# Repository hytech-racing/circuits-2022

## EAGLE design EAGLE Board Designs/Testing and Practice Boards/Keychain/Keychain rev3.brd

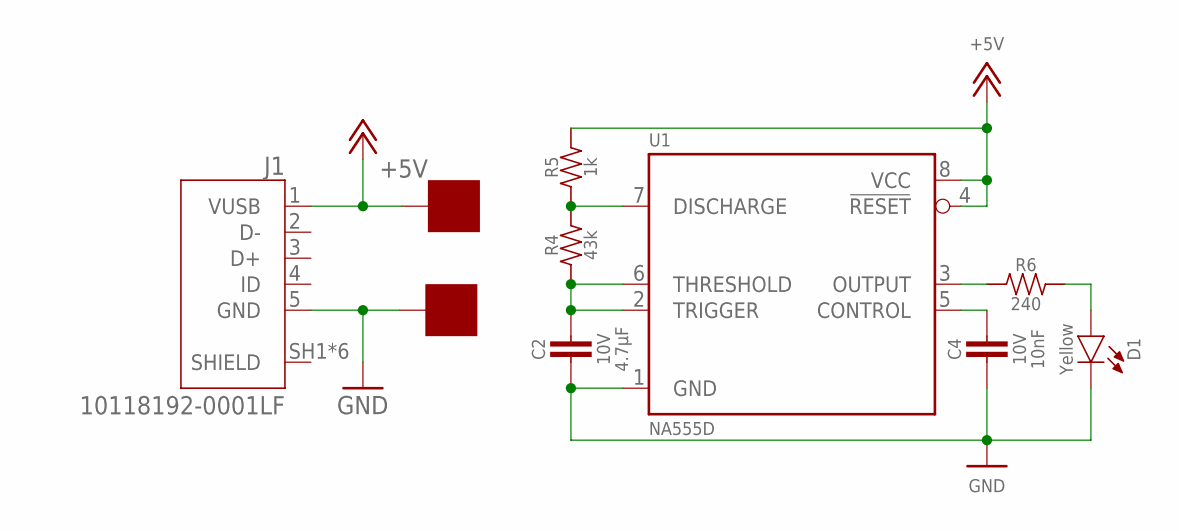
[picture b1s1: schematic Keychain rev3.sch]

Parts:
5V: SOLDER_PAD; SOLDER_PAD_XSMALL
C2: CAPACITOR_0603_10V_4.7UF; 0603-CAP
C4: CAPACITOR_0603_10V_10NF; 0603-CAP
D1: LED_0603_YELLOW; 0603-LED
GND: SOLDER_PAD; SOLDER_PAD_XSMALL
J1: 10118192-0001LF; AMPHENOL_10118192-0001LF
R4: RESISTOR_0603_43K; 0603-RES
R5: RESISTOR_0603_1K; 0603-RES
R6: RESISTOR_0603_240; 0603-RES
U1: NA555; SOIC-08(NARROW,0.15")

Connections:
+5V: 5V.P$1, J1.1 (VUSB), R5.2, U1.4 (!RESET), U1.8 (VCC)
GND: C2.2, C4.2, D1.1 (C), GND.P$1, J1.5 (GND), U1.1 (GND)
unnamed: C2.1, R4.1, U1.2 (TRIGGER), U1.6 (THRESHOLD)
unnamed: R4.2, R5.1, U1.7 (DISCHARGE)
unnamed: R6.1, U1.3 (OUTPUT)
unnamed: D1.2 (A), R6.2
unnamed: C4.1, U1.5 (CONTROL)

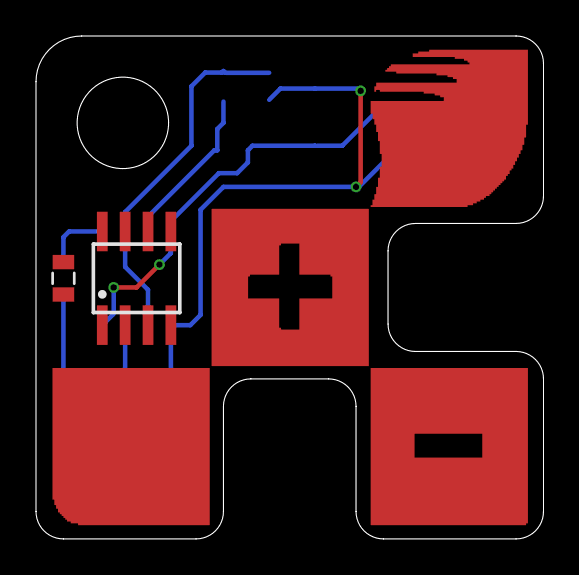
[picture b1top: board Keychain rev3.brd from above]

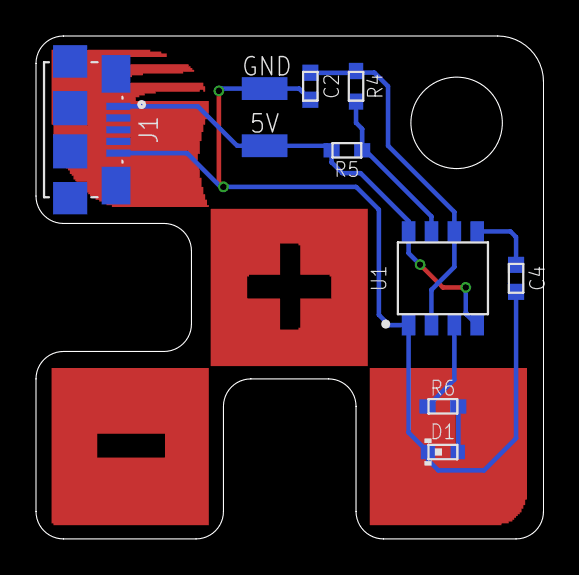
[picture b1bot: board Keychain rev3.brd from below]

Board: 2 copper layers, 28.2 x 27.9 mm, 12 parts (10 on the bottom side), 7 nets.

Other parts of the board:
E$1: 0805@1
E$2: SOIC-08

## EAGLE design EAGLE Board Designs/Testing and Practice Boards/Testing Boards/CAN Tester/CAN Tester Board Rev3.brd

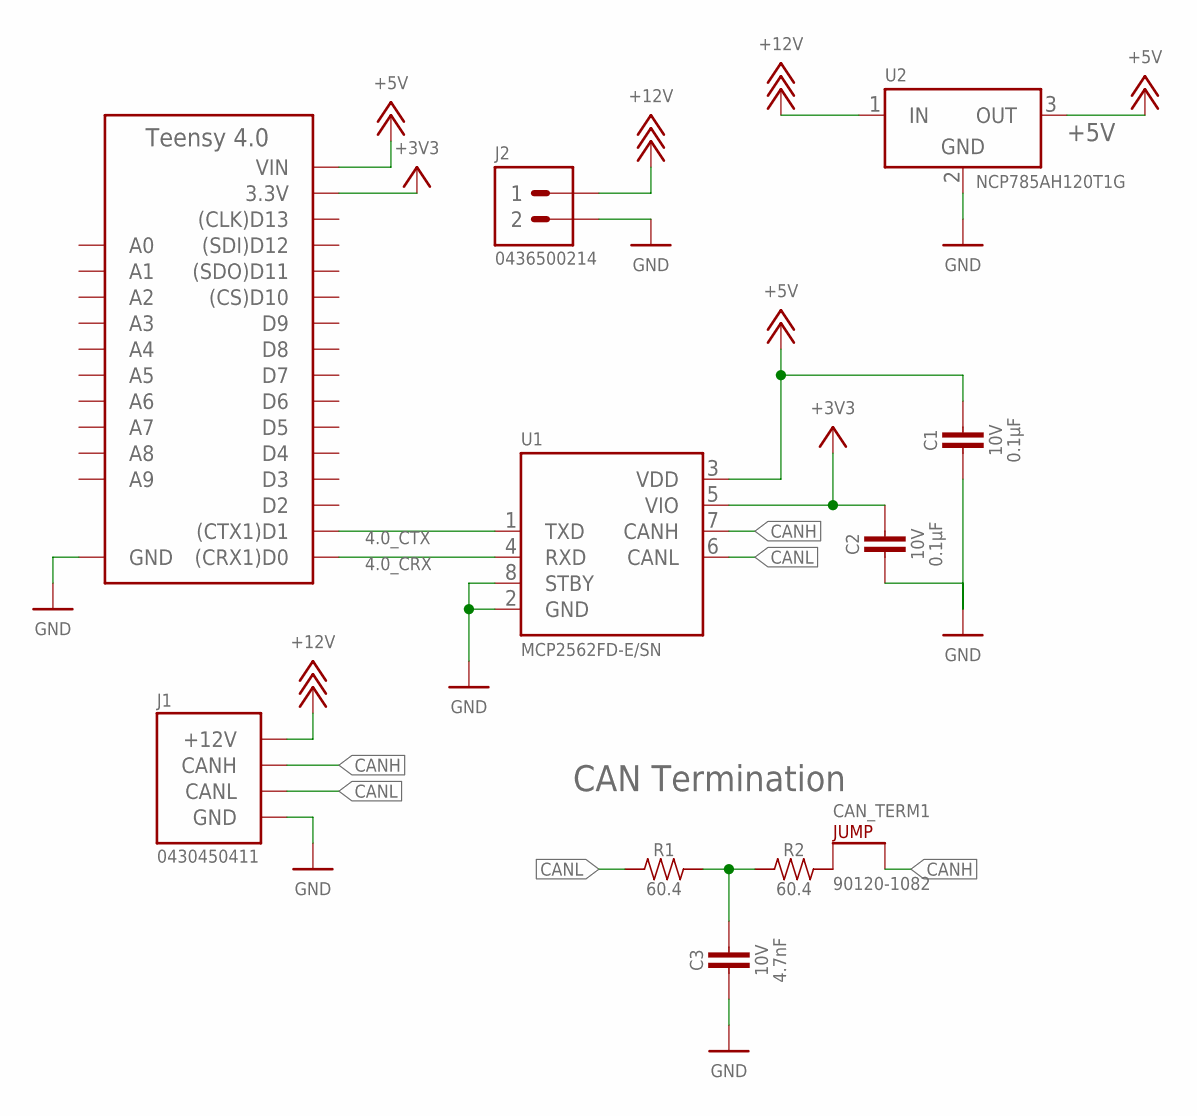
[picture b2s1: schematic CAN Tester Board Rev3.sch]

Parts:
A1: TEENSY_4.0; TEENSY_SHORT
C1, C2: CAPACITOR_0603_10V_0.1UF; 0603-CAP
C3: CAPACITOR_0603_10V_4.7NF; 0603-CAP
CAN_TERM1: JUMPER__1X02; 1X02
J1: CONNECTOR-CAN_μF_S_RA_; MOLEX_MICROFIT_SMD_RIGHTANGLE_04_DUAL
J2: CONNECTOR-2_MICROFIT_SMD_RIGHTANGLE_02_SINGLE_BLA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; MOLEX_MICROFIT_SMD_RIGHTANGLE_02_SINGLE
R1, R2: RESISTOR_0603_60.4; 0603-RES
U1: MCP2562FD; SOIC-08(NARROW,0.15")
U2: VOLTAGE_REGULATOR_SOT-89_12V; SOT-89

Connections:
4.0_CRX: A1.D0 ((CRX1)D0), U1.4 (RXD)
4.0_CTX: A1.D1 ((CTX1)D1), U1.1 (TXD)
+3V3: A1.3.3V, C2.1, U1.5 (VIO)
+5V: A1.VIN, C1.1, U1.3 (VDD), U2.3 (OUT)
+12V: J1.1 (+12V), J2.1, U2.1 (IN)
CANH: CAN_TERM1.2, J1.4 (CANH), U1.7 (CANH)
CANL: J1.3 (CANL), R1.1, U1.6 (CANL)
GND: A1.AGND/GND (GND), A1.GND, C1.2, C2.2, C3.2, J1.2 (GND), J2.2, U1.2 (GND), U1.8 (STBY), U2.2 (GND)
unnamed: C3.1, R1.2, R2.1
unnamed: CAN_TERM1.1, R2.2

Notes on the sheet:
CAN Termination

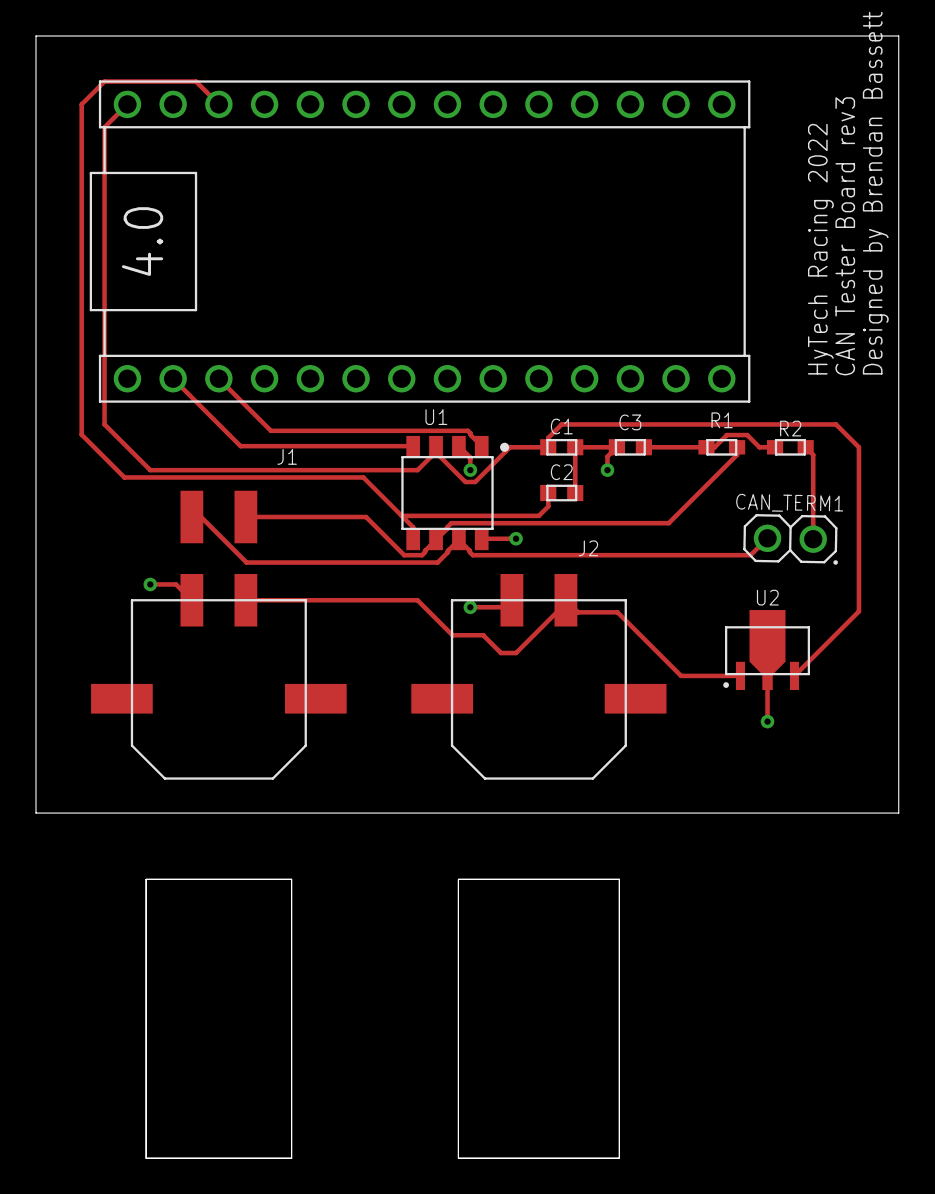
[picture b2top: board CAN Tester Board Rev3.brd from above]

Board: 2 copper layers, 47.9 x 43.2 mm, 11 parts (0 on the bottom side), 10 nets.

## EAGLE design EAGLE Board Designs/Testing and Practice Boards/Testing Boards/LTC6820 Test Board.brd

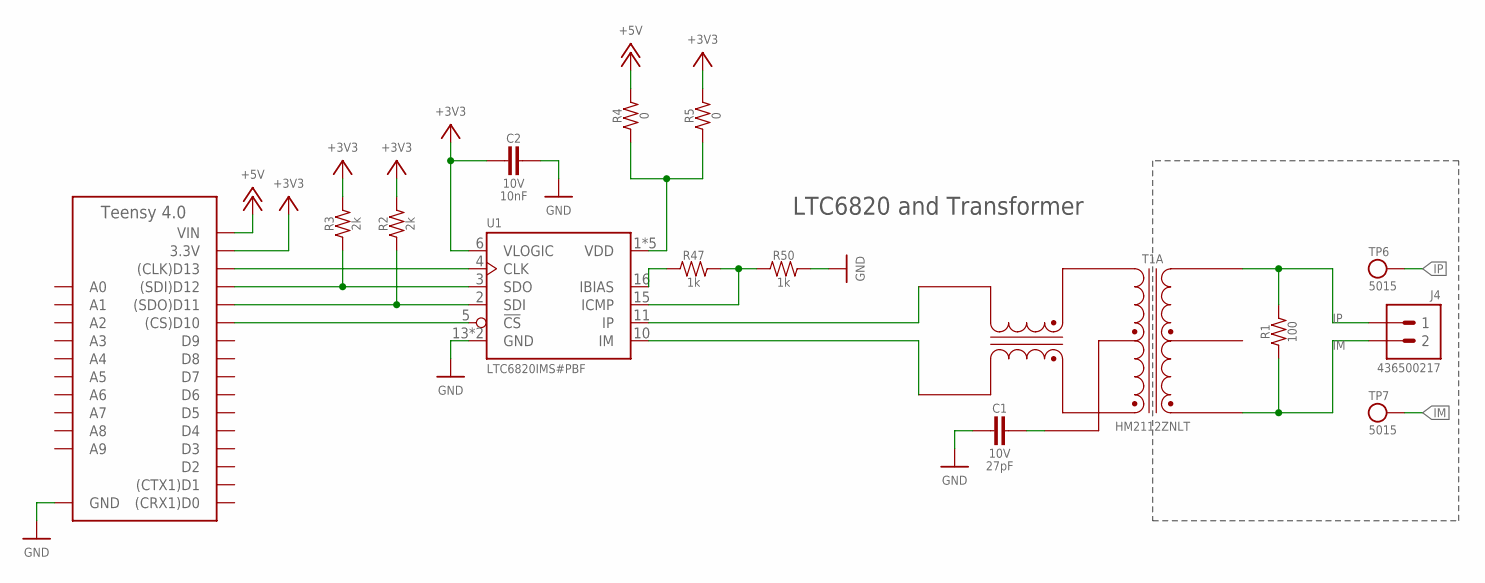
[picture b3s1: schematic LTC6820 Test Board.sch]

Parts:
A1: TEENSY_4.0; TEENSY_SHORT
C1: CAPACITOR_0603_10V_27PF; 0603-CAP
C2: CAPACITOR_0603_10V_10NF; 0603-CAP
J4: CONNECTOR-2_MF_T_V_; MOLEX_MICROFIT_PTH_VERTICAL_02_SINGLE
R1: RESISTOR_0603_100; 0603-RES
R2, R3: RESISTOR_0603_2K; 0603-RES
R4, R5: RESISTOR_0603_0; 0603-RES
R47, R50: RESISTOR_0603_1K; 0603-RES
T1: TRANSFORMER_HM2112ZNLT_AIRGAP; HM2112ZNLT_AIRGAP
TP6, TP7: TEST_POINT; MICRO_MINIATURE
U1: LTC6820; MSOP-16

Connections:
+3V3: A1.3.3V, C2.2, R2.2, R3.2, R5.2, U1.6 (VLOGIC)
+5V: A1.VIN, R4.2
GND: A1.AGND/GND (GND), A1.GND, C1.2, C2.1, R50.2, U1.13 (GND), U1.14 (GND)
IM: J4.2, R1.1, T1.1 (MX+), TP7.1
IP: J4.1, R1.2, T1.3 (MX-), TP6.1
unnamed: C1.1, T1.11 (TCT)
unnamed: A1.D13 ((CLK)D13), U1.4 (CLK)
unnamed: A1.D12 ((SDI)D12), R3.1, U1.3 (SDO)
unnamed: A1.D11 ((SDO)D11), R2.1, U1.2 (SDI)
unnamed: A1.D10 ((CS)D10), U1.5 (!CS)
unnamed: R4.1, R5.1, U1.1 (VDD), U1.7 (VDD), U1.8 (VDD), U1.9 (VDD), U1.12 (VDD)
unnamed: T1.10 (TD-), U1.11 (IP)
unnamed: R47.1, U1.16 (IBIAS)
unnamed: R47.2, R50.1, U1.15 (ICMP)
unnamed: T1.12 (TD+), U1.10 (IM)

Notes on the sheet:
LTC6820 and Transformer

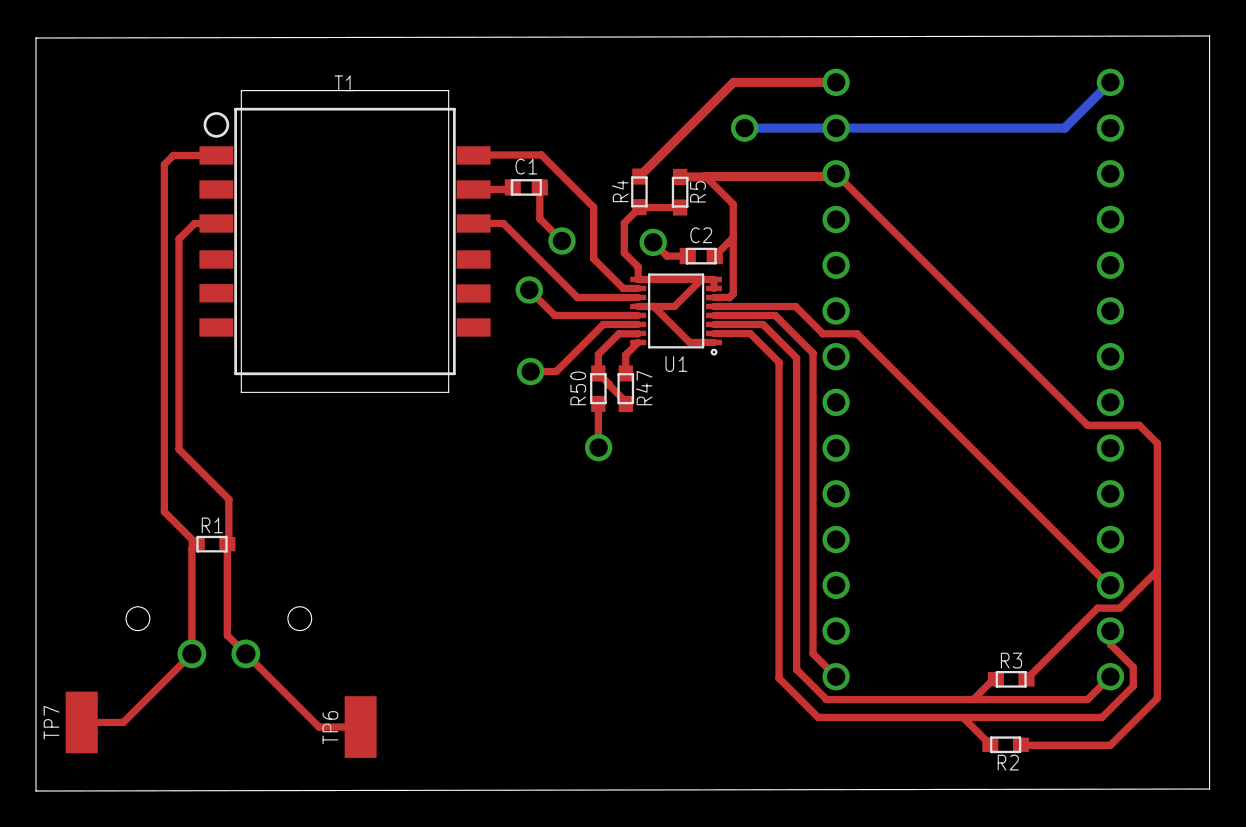
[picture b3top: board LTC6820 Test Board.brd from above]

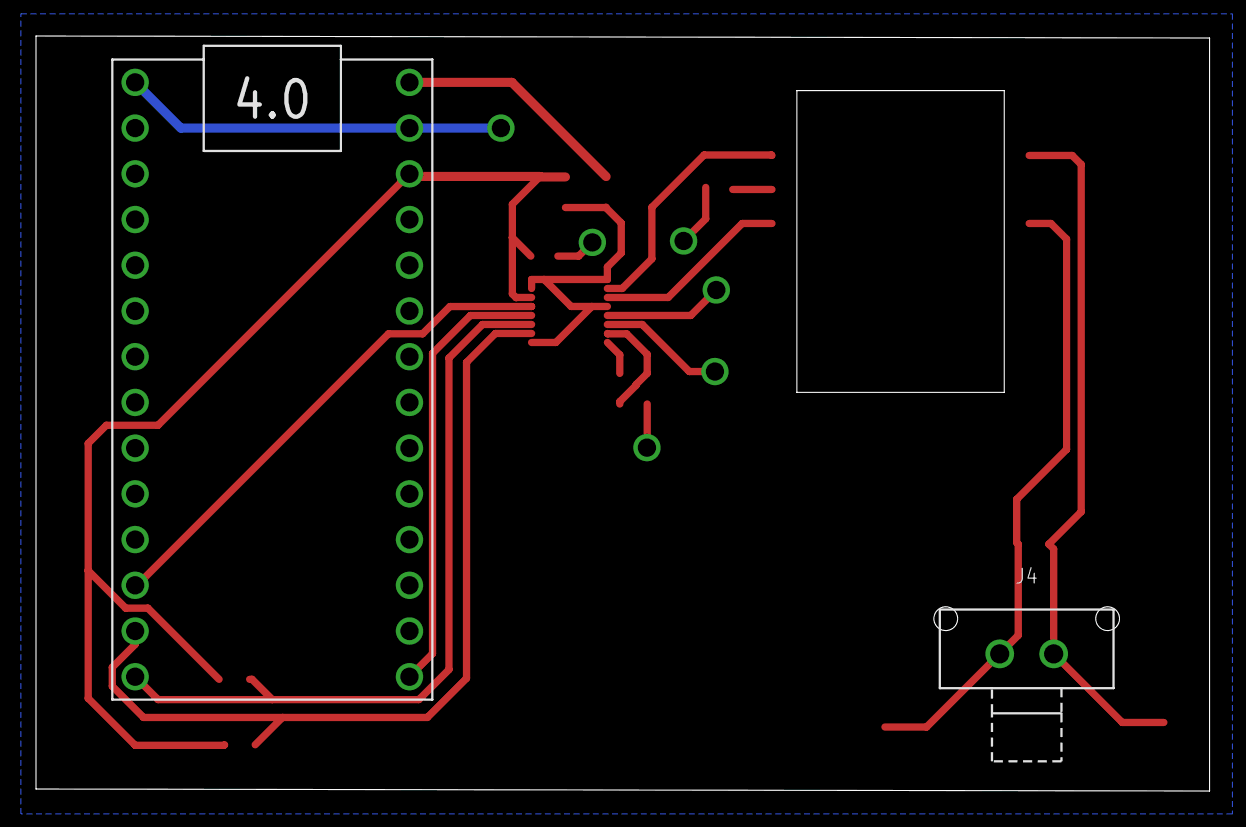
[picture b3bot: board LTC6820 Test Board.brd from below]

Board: 2 copper layers, 65.2 x 41.9 mm, 15 parts (2 on the bottom side), 15 nets.

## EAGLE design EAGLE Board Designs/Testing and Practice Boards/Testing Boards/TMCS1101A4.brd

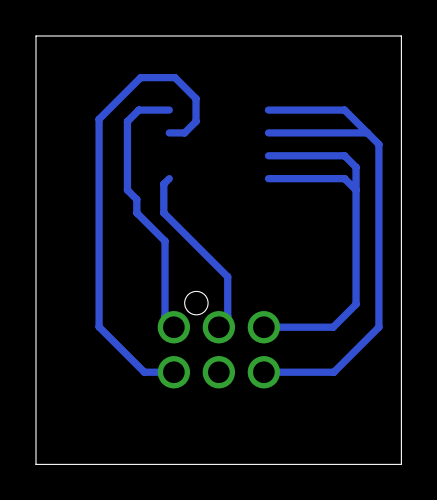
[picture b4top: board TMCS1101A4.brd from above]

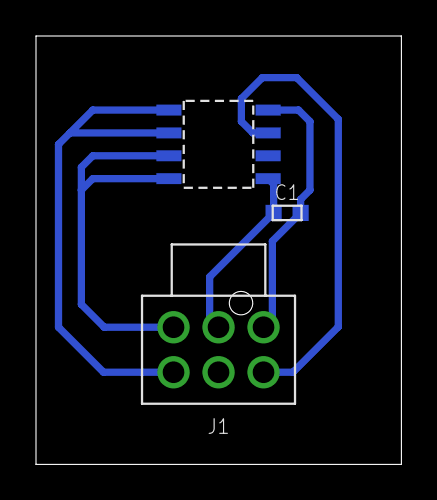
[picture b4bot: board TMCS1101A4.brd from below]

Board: 2 copper layers, 20.3 x 23.8 mm, 3 parts (3 on the bottom side), 5 nets.

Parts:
C1: CAPACITOR_0603_10V_0.1UF; 0603-CAP
J1: CONNECTOR-6_NF_T_V_BLACK; MOLEX_NANOFIT_PTH_06
U$1: TMCS1101A4; SOIC8

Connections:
+5V: C1.2, J1.1, U$1.P$8
GND: C1.1, J1.2, U$1.P$5
IN+: J1.6, U$1.P$1, U$1.P$2
IN-: J1.3, U$1.P$3, U$1.P$4
VOUT: J1.4, U$1.P$7

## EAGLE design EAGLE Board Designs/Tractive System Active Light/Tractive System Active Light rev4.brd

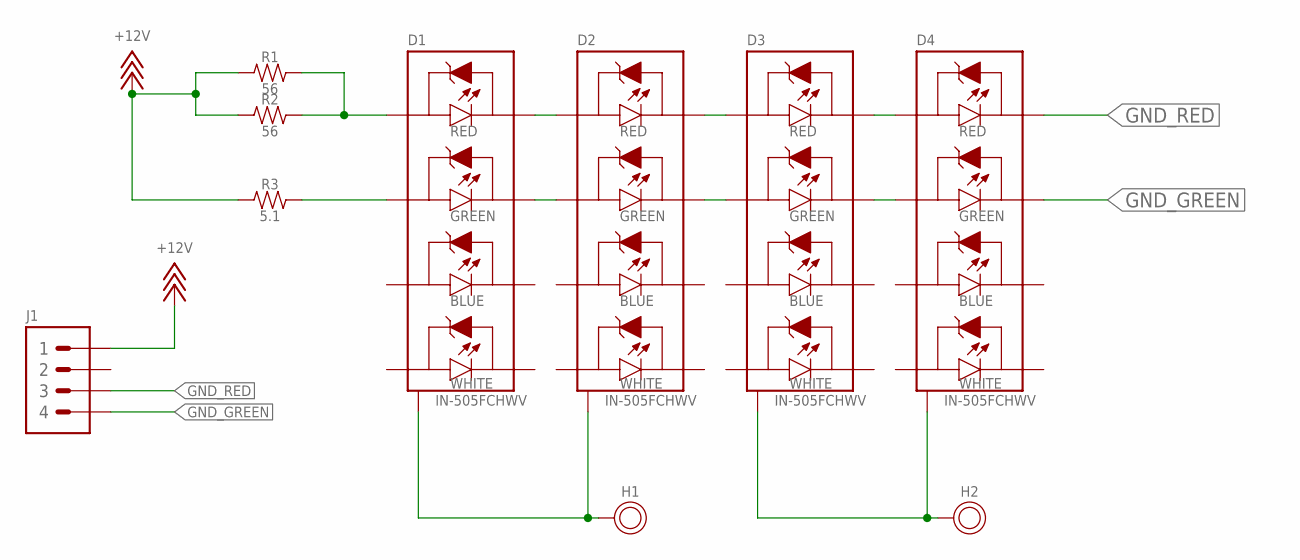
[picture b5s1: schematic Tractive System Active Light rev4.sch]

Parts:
D1, D2, D3, D4: LED_RGBW_IN-505FCHWV; IN-505FCHWV
H1, H2: MOUNTING_HEATSINK_M3; MOUNTING_M3
J1: CONNECTOR-4_μF_S_RA_; MOLEX_MICROFIT_SMD_RIGHTANGLE_04_DUAL
R1, R2: RESISTOR_0805_56; 0805-RES
R3: RESISTOR_0603_5.1; 0603-RES

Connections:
+12V: J1.1, R1.1, R2.1, R3.1
GND_GREEN: D4.B- (GREEN-), J1.4
GND_RED: D4.A- (RED-), J1.3
unnamed: D3.A- (RED-), D4.A+ (RED+)
unnamed: D3.B- (GREEN-), D4.B+ (GREEN+)
unnamed: D2.A- (RED-), D3.A+ (RED+)
unnamed: D2.B- (GREEN-), D3.B+ (GREEN+)
unnamed: D1.A- (RED-), D2.A+ (RED+)
unnamed: D1.B- (GREEN-), D2.B+ (GREEN+)
unnamed: D1.A+ (RED+), R1.2, R2.2
unnamed: D1.THERMAL, D2.THERMAL, H1.P$1
unnamed: D1.B+ (GREEN+), R3.2
unnamed: D3.THERMAL, D4.THERMAL, H2.P$1

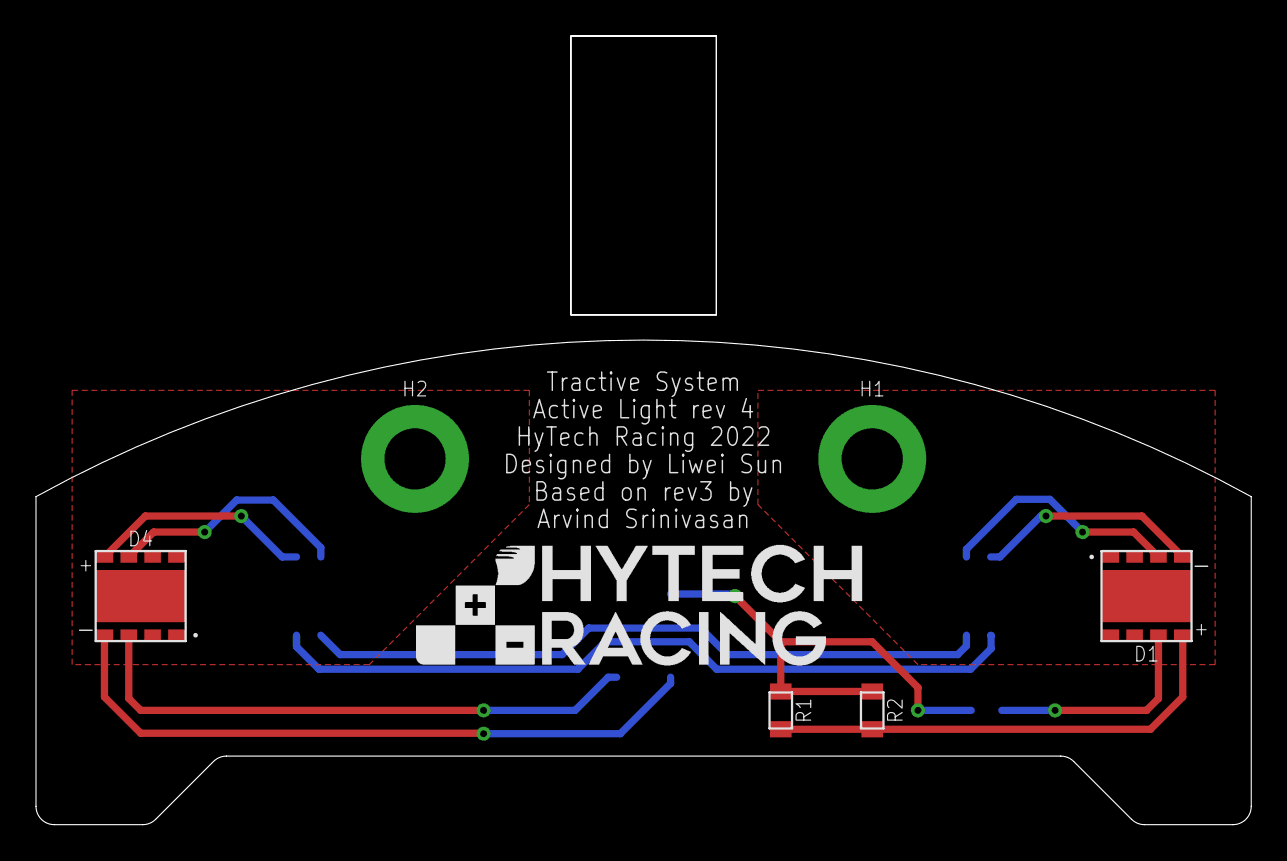
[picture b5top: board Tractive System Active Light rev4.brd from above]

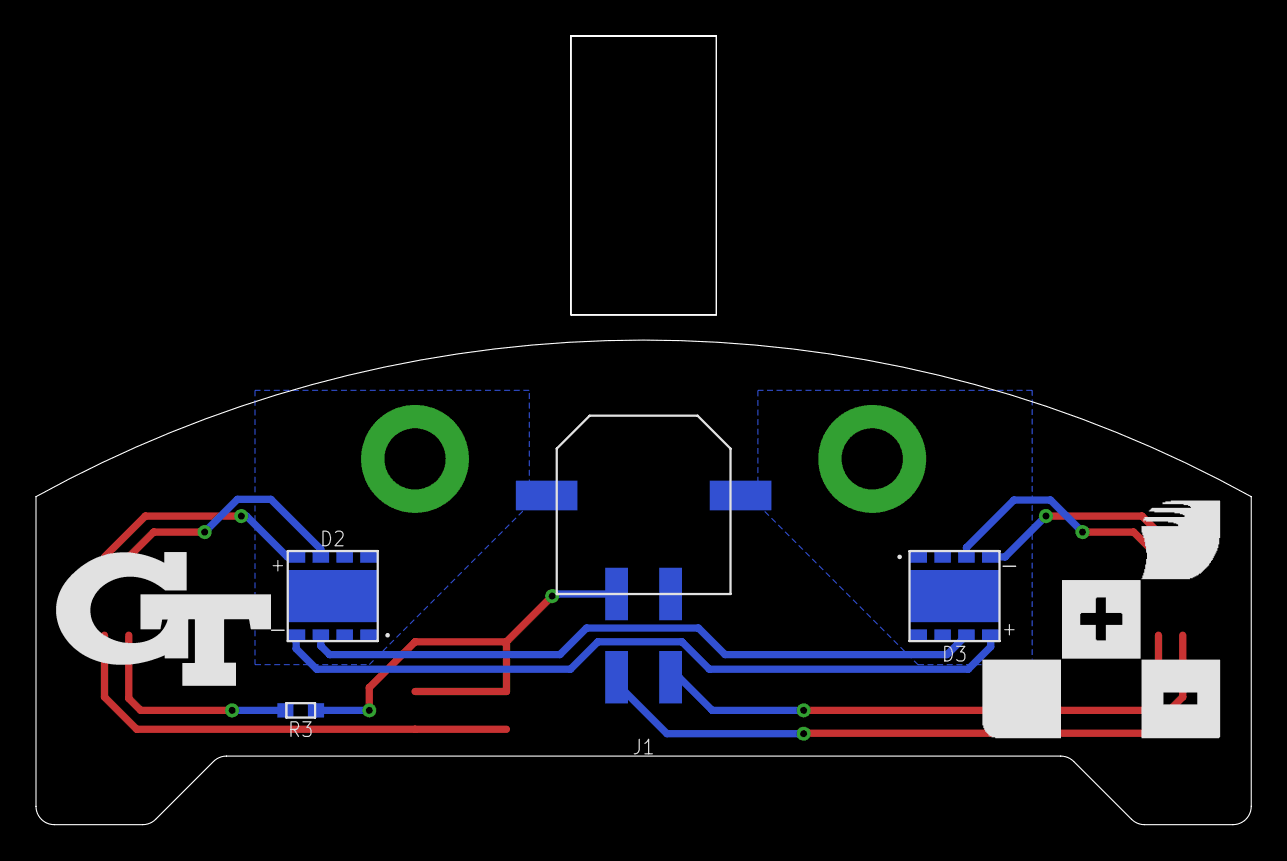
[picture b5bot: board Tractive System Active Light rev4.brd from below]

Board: 2 copper layers, 67.5 x 26.9 mm, 13 parts (6 on the bottom side), 13 nets.

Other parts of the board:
U$1: LOGO_HYTECH_SQUARE_EXTRA_LARGE
U$2: LOGO_HYTECH_MEDIUM
U$3: LOGO_GT_MEDIUM

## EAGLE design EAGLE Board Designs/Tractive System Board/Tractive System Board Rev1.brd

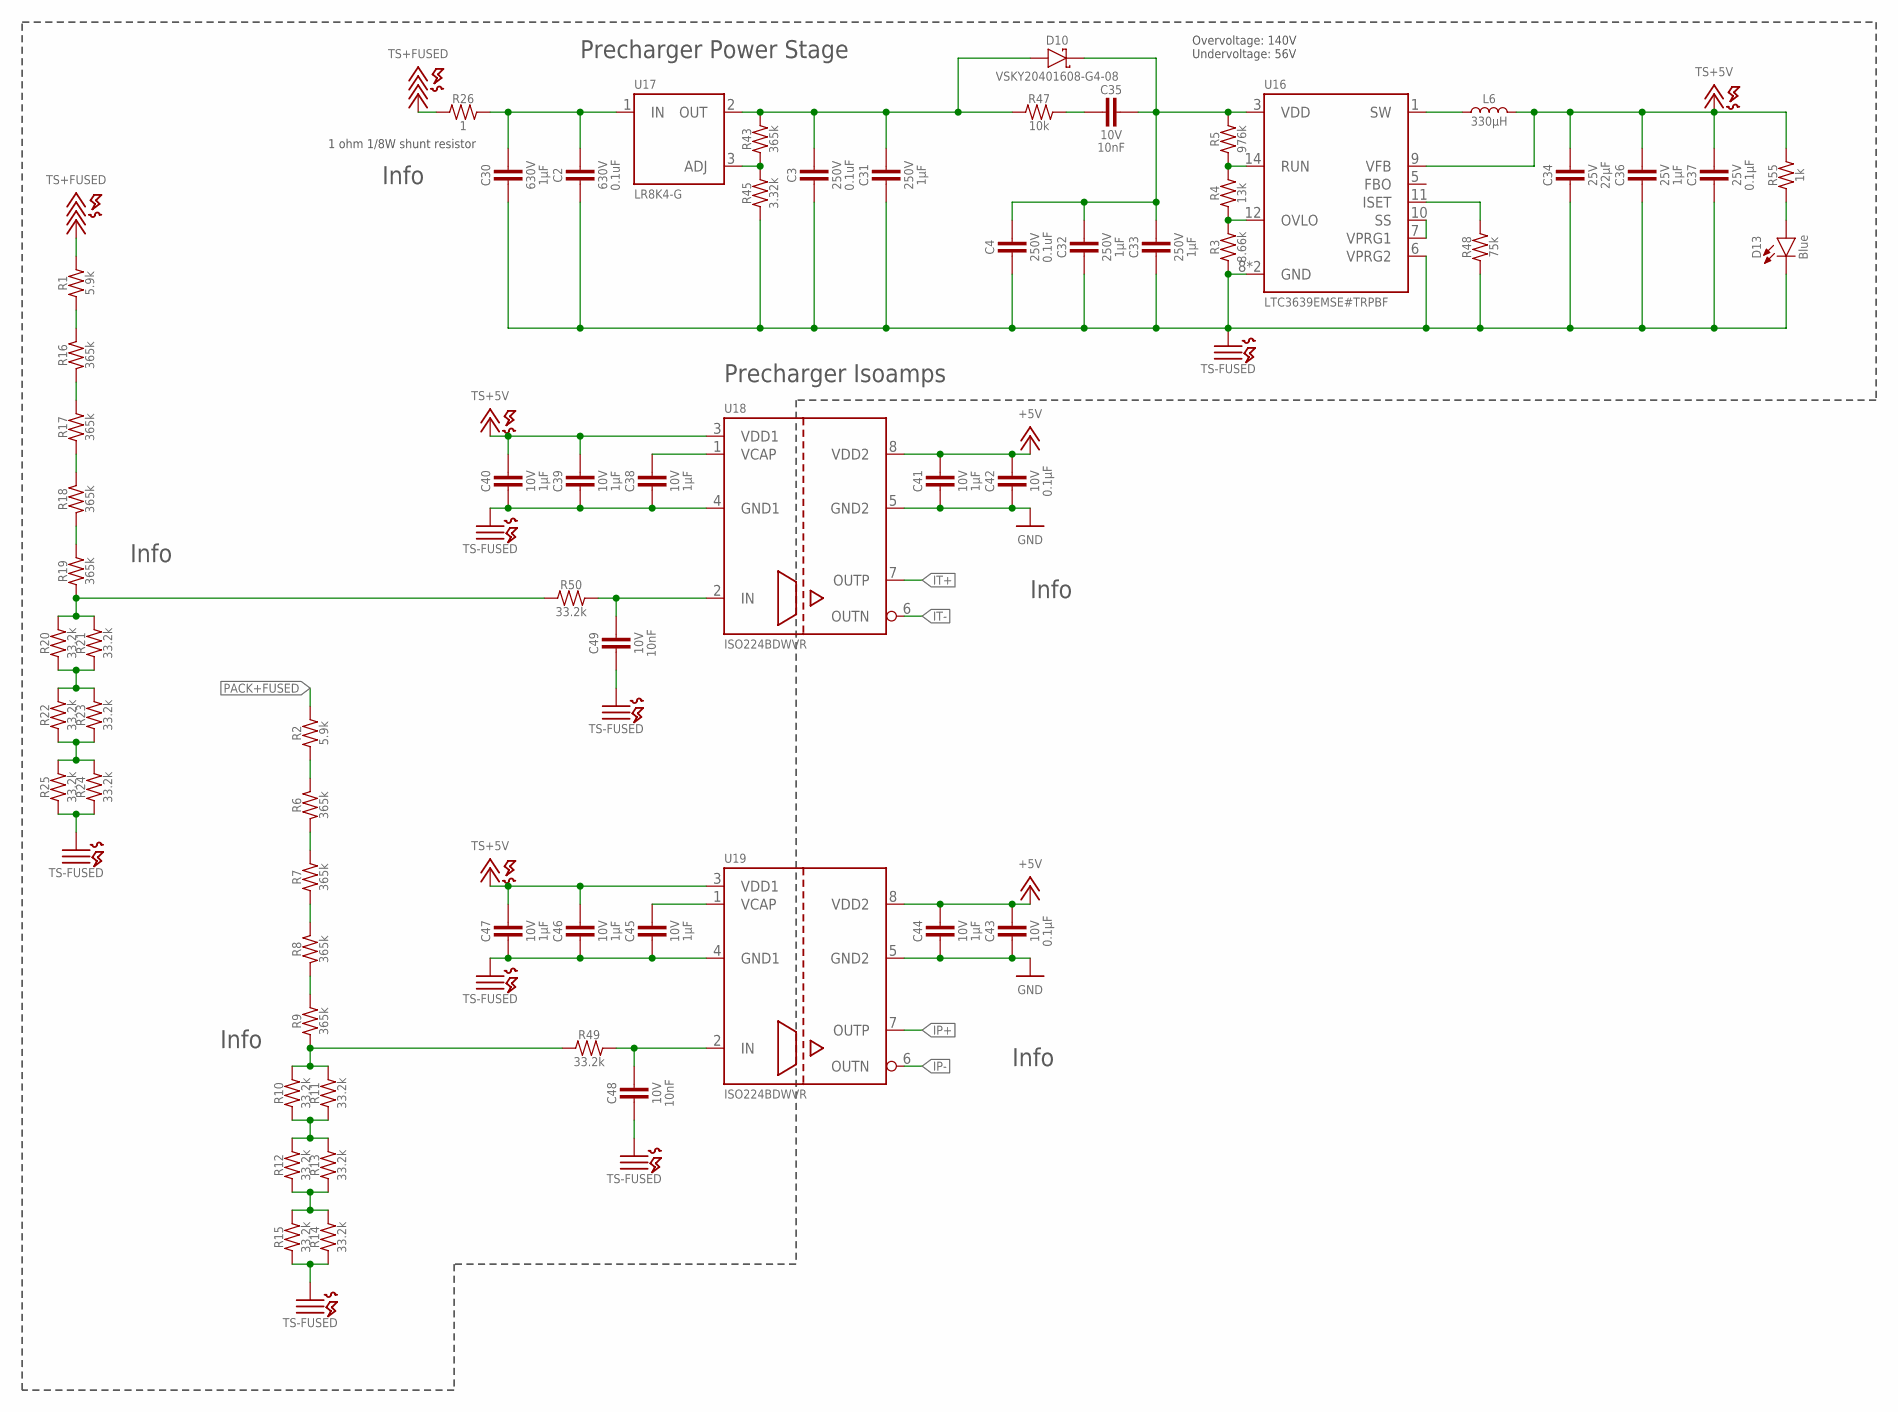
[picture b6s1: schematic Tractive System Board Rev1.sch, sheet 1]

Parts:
C2: CAPACITOR_2220_630V_0.1UF; 2220-CAP
C3, C4: CAPACITOR_1206_250V_0.1UF; 1206-CAP
C30: CAPACITOR_2220_630V_1UF; 2220-CAP
C31, C32, C33: CAPACITOR_2220_250V_1UF; 2220-CAP
C34: CAPACITOR_0805_25V_22UF; 0805-CAP
C35, C48, C49: CAPACITOR_0603_10V_10NF; 0603-CAP
C36: CAPACITOR_0603_25V_1UF; 0603-CAP
C37: CAPACITOR_0603_25V_0.1UF; 0603-CAP
C38, C39, C40, C41, C44, C45, C46, C47: CAPACITOR_0603_10V_1UF; 0603-CAP
C42, C43: CAPACITOR_0603_10V_0.1UF; 0603-CAP
D10: SCHOTTKY; CLP1608-2L
D13: LED_0603_BLUE; 0603-LED
L6: INDUCTOR_SRU1048_330UH; SRU1048
R1, R2: RESISTOR_0603_5.9K; 0603-RES
R3: RESISTOR_0603_8.66K; 0603-RES
R4: RESISTOR_0603_13K; 0603-RES
R5: RESISTOR_0805_976K; 0805-RES
R6, R7, R8, R9, R16, R17, R18, R19, R43: RESISTOR_0805_365K; 0805-RES
R10, R11, R12, R13, R14, R15, R20, R21, R22, R23, R24, R25, R49, R50: RESISTOR_0603_33.2K; 0603-RES
R26: RESISTOR_0805_1; 0805-RES
R45: RESISTOR_0603_3.32K; 0603-RES
R47: RESISTOR_0603_10K; 0603-RES
R48: RESISTOR_0603_75K; 0603-RES
R55: RESISTOR_0603_1K; 0603-RES
U16: LTC3639; MSE16(12)
U17: VOLTAGE_REGULATOR_ADJ_LR8_DPAK; DPAK(2-7K1S)
U18, U19: ISO224B_AIRGAP; SOIC-08(WIDE,0.295")-AIRGAP

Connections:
+5V: C41.1, C42.1, C43.1, C44.1, U18.8 (VDD2), U19.8 (VDD2); also elsewhere on the board
GND: C41.2, C42.2, C43.2, C44.2, U18.5 (GND2), U19.5 (GND2); also elsewhere on the board
IP+: U19.7 (OUTP); also elsewhere on the board
IP-: U19.6 (OUTN); also elsewhere on the board
IT+: U18.7 (OUTP); also elsewhere on the board
IT-: U18.6 (OUTN); also elsewhere on the board
unnamed: R3.2, R4.1, U16.12 (OVLO)
unnamed: R4.2, R5.1, U16.14 (RUN)
unnamed: R6.2, R7.2
unnamed: R7.1, R8.1
unnamed: R1.1, R16.1
unnamed: R2.1, R6.1
unnamed: R8.2, R9.2
unnamed: R20.1, R21.1, R22.2, R23.2
unnamed: R9.1, R10.2, R11.2, R49.1
unnamed: C2.1, C30.1, R26.2, U17.1 (IN)
unnamed: R16.2, R17.2
unnamed: R17.1, R18.1
unnamed: R18.2, R19.2
unnamed: R19.1, R20.2, R21.2, R50.1
unnamed: R12.1, R13.1, R14.2, R15.2
unnamed: R22.1, R23.1, R24.2, R25.2
unnamed: R10.1, R11.1, R12.2, R13.2
unnamed: D13.2 (A), R55.1
unnamed: R43.1, R45.2, U17.3 (ADJ)
unnamed: C3.1, C31.1, D10.2 (A), R43.2, R47.1, U17.2 (OUT)
unnamed: C35.2, R47.2
unnamed: C4.1, C32.1, C33.1, C35.1, D10.1 (C), R5.2, U16.3 (VDD)
unnamed: C48.1, R49.2, U19.2 (IN)
unnamed: C49.1, R50.2, U18.2 (IN)
unnamed: R48.2, U16.11 (ISET)
unnamed: L6.1, U16.1 (SW)
unnamed: C45.1, U19.1 (VCAP)
unnamed: C38.1, U18.1 (VCAP)
unnamed: U16.7 (VPRG1), U16.10 (SS)
PACK+FUSED: R2.2; also elsewhere on the board
TS+5V: C34.1, C36.1, C37.1, C39.1, C40.1, C46.1, C47.1, L6.2, R55.2, U16.9 (VFB), U18.3 (VDD1), U19.3 (VDD1); also elsewhere on the board
TS+FUSED: R1.2, R26.1; also elsewhere on the board
TS-FUSED: C2.2, C3.2, C4.2, C30.2, C31.2, C32.2, C33.2, C34.2, C36.2, C37.2, C38.2, C39.2, C40.2, C45.2, C46.2, C47.2, C48.2, C49.2, D13.1 (C), R3.1, R14.1, R15.1, R24.1, R25.1, R45.1, R48.1, U16.6 (VPRG2), U16.8 (GND), U16.16 (GND), U18.4 (GND1), U19.4 (GND1); also elsewhere on the board

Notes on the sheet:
Precharger Power Stage
Precharger Isoamps
1 ohm 1/8W shunt resistor
Overvoltage: 140V Undervoltage: 56V
Info

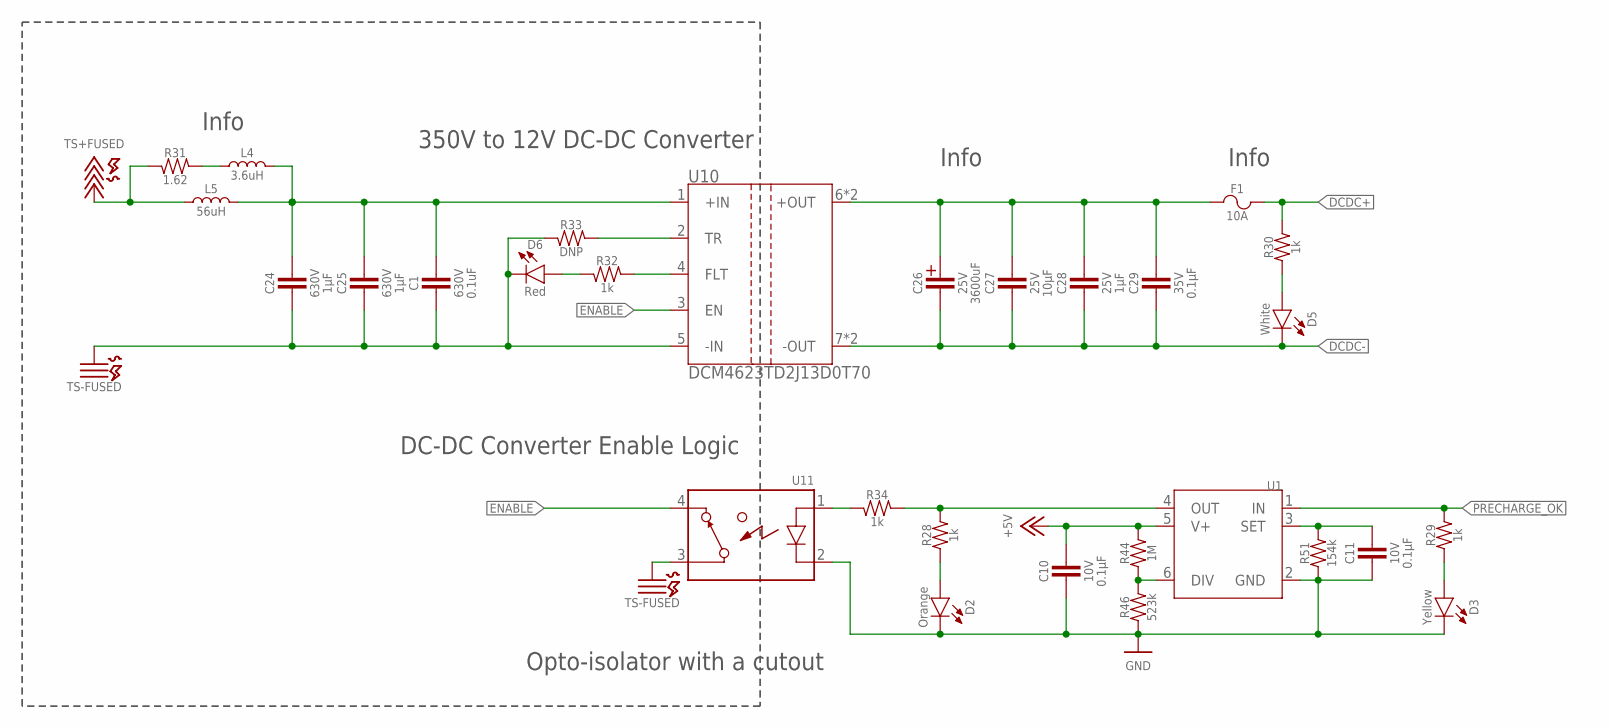
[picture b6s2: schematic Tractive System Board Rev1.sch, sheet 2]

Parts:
C1: CAPACITOR_2220_630V_0.1UF; 2220-CAP
C10, C11: CAPACITOR_0603_10V_0.1UF; 0603-CAP
C24, C25: CAPACITOR_2220_630V_1UF; 2220-CAP
C26: CAPACITOR_POLAR__3600UF; EKYC*MM
C27: CAPACITOR_0603_25V_10UF; 0603-CAP
C28: CAPACITOR_0603_25V_1UF; 0603-CAP
C29: CAPACITOR_0603_35V_0.1UF; 0603-CAP
D2: LED_0603_ORANGE; 0603-LED
D3: LED_0603_YELLOW; 0603-LED
D5: LED_0603_WHITE; 0603-LED
D6: LED_0603_RED; 0603-LED
F1: FUSE_MB_10; MINI-BLADE_FUSE_HOLDER
L4: INDUCTOR_PA4334_3.6UH; PA4334
L5: INDUCTOR_WELMHI_56UH; WE-LMHI
R28, R29, R30, R32, R34: RESISTOR_0603_1K; 0603-RES
R31: RESISTOR_0603_1.62; 0603-RES
R33: RESISTOR_0603_DNP; 0603-RES
R44: RESISTOR_0805_1M; 0805-RES
R46: RESISTOR_0805_523K; 0805-RES
R51: RESISTOR_0603_154K; 0603-RES
U1: LTC6994_1; SOT-23-6
U10: DCM4623TD2J13D0T70; DCM4623
U11: RELAY_SOLIDSTATE_NC_AG; DIP-4_AIRGAP

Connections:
+5V: C10.1, R44.2, U1.5 (V+); also elsewhere on the board
DCDC+: F1.L1 (1), F1.L2 (1), R30.2; also elsewhere on the board
DCDC-: C26.- (MINUS), C27.1, C28.1, C29.1, D5.1 (C), U10.7 (-OUT), U10.9 (-OUT); also elsewhere on the board
ENABLE: U10.3 (EN), U11.4 (CONTACT2)
GND: C10.2, C11.2, D2.1 (C), D3.1 (C), R46.1, R51.1, U1.2 (GND), U11.2 (CONTROL-); also elsewhere on the board
unnamed: R44.1, R46.2, U1.6 (DIV)
unnamed: R34.2, U11.1 (CONTROL+)
unnamed: C11.1, R51.2, U1.3 (SET)
unnamed: R28.2, R34.1, U1.4 (OUT)
unnamed: D2.2 (A), R28.1
unnamed: D5.2 (A), R30.1
unnamed: D3.2 (A), R29.1
unnamed: L4.2, R31.1
unnamed: C1.1, C24.1, C25.1, L4.1, L5.1, U10.1 (+IN)
unnamed: D6.2 (A), R32.2
unnamed: R32.1, U10.4 (FLT)
unnamed: R33.1, U10.2 (TR)
unnamed: C26.+ (PLUS), C27.2, C28.2, C29.2, F1.R1 (2), F1.R2 (2), U10.6 (+OUT), U10.8 (+OUT)
PRECHARGE_OK: R29.2, U1.1 (IN); also elsewhere on the board
TS+FUSED: L5.2, R31.2; also elsewhere on the board
TS-FUSED: C1.2, C24.2, C25.2, D6.1 (C), R33.2, U10.5 (-IN), U11.3 (CONTACT1); also elsewhere on the board

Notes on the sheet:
350V to 12V DC-DC Converter
DC-DC Converter Enable Logic
Opto-isolator with a cutout
Info
